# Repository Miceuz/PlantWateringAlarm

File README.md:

PlantWateringAlarm
==================

A soil moisture level sensor based on ATTINY44. Uses capacitive sensing.

More info at http://wemakethings.net/chirp

Contact: mic a wemakethings.net

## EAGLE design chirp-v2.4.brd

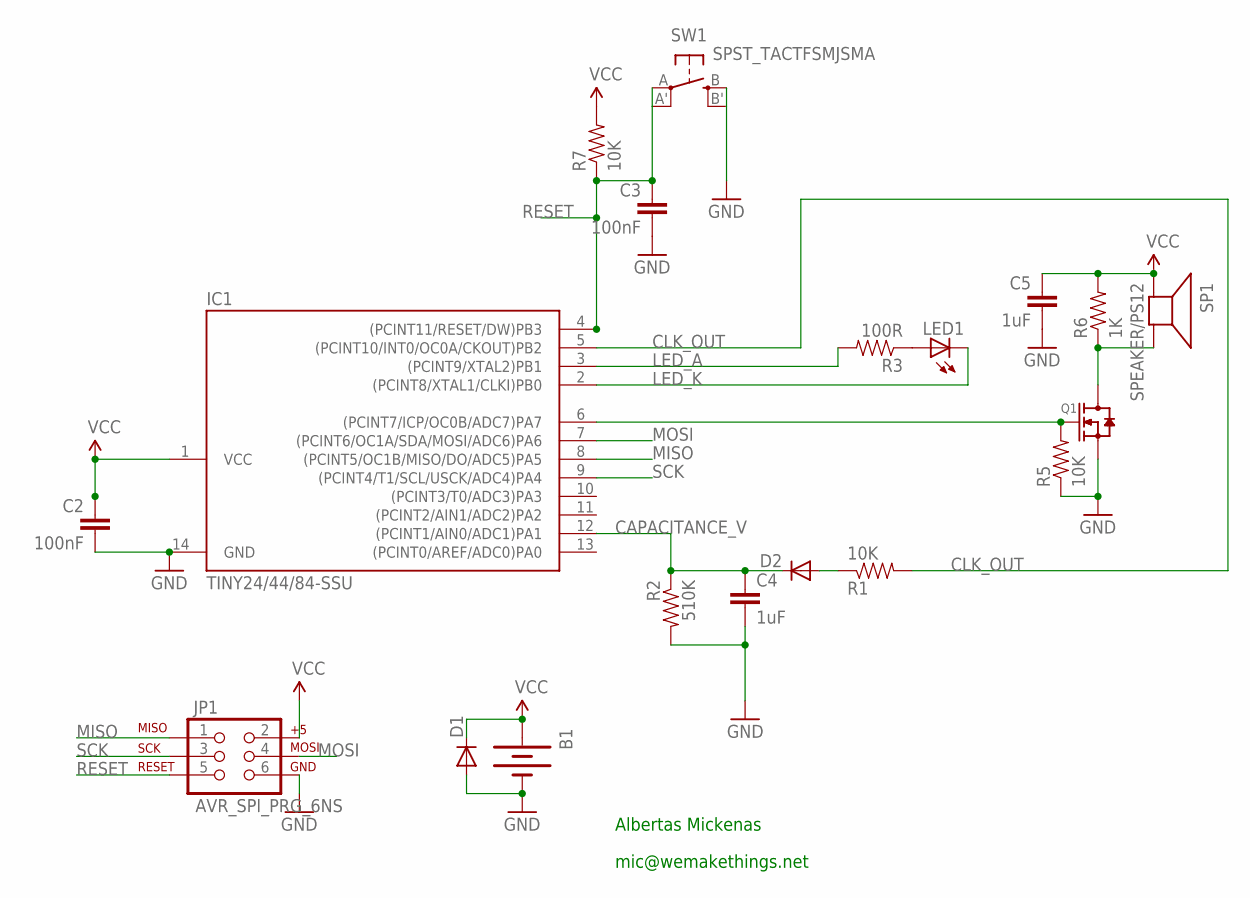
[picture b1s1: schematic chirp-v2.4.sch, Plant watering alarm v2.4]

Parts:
B1: BATTERY; BAT-HLD-001
C2, C3: 100nF; 0603-CAP
C4, C5: 1uF; 0603-CAP
D1: DIODE-DO214AC; DO214AC
D2: DIODE-SCHOTTKY_; SOD-523
IC1: TINY24/44/84-SSU; SOIC14
JP1: AVR_SPI_PRG_6NS; 2X3-NS
LED1: LEDCHIPLED_0805; CHIPLED_0805
Q1: MOSFET-N-SOT23; SOT23
R1, R5, R7: 10K; 0603-RES
R2: 510K; 0603-RES
R3: 100R; 0603-RES
R6: 1K; 0603-RES
SP1: SPEAKER/PS12; PS12
SW1: SPST_TACTFSMJSMA; FSMJSMA

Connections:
BUZZER: IC1.6 ((PCINT7/ICP/OC0B/ADC7)PA7), Q1.1 (G), R5.2
CAPACITANCE_V: C4.1, D2.K (C), IC1.12 ((PCINT1/AIN0/ADC1)PA1), R2.1
CLK_OUT: IC1.5 ((PCINT10/INT0/OC0A/CKOUT)PB2), R1.2
GND: B1.2 (-), C2.2, C3.2, C4.2, C5.2, D1.A, IC1.14 (GND), JP1.6, Q1.2 (S), R2.2, R5.1, SW1.B (S), SW1.B' (S1)
LED_A: IC1.3 ((PCINT9/XTAL2)PB1), R3.2
LED_K: IC1.2 ((PCINT8/XTAL1/CLKI)PB0), LED1.C
MISO: IC1.8 ((PCINT5/OC1B/MISO/DO/ADC5)PA5), JP1.1
MOSI: IC1.7 ((PCINT6/OC1A/SDA/MOSI/ADC6)PA6), JP1.4
unnamed: Q1.3 (D), R6.1, SP1.P$2 (-)
unnamed: LED1.A, R3.1
RESET: C3.1, IC1.4 ((PCINT11/RESET/DW)PB3), JP1.5, R7.1, SW1.A, SW1.A' (P1)
SCK: IC1.9 ((PCINT4/T1/SCL/USCK/ADC4)PA4), JP1.3
VCC: B1.1 (+), C2.1, C5.1, D1.C, IC1.1 (VCC), JP1.2, R6.2, R7.2, SP1.P$1 (+)
V_CAP: D2.A, R1.1

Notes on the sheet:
Albertas Mickenas
mic@wemakethings.net

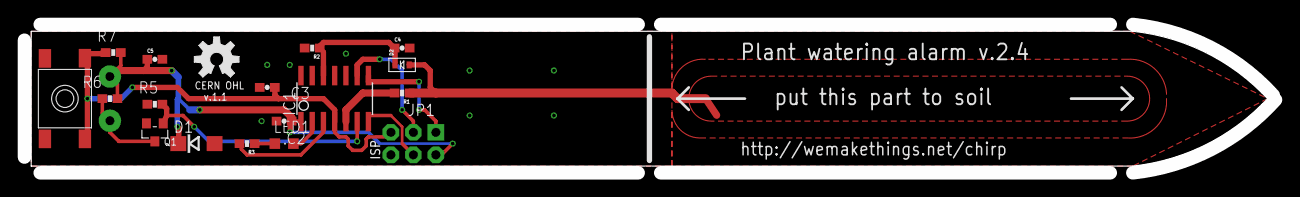
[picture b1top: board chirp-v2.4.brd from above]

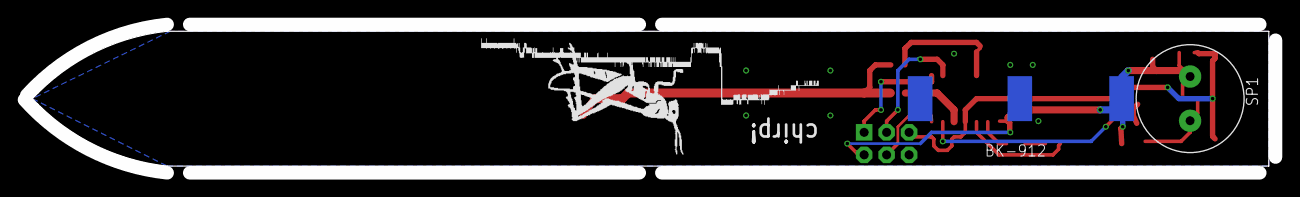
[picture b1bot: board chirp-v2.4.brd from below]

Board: 2 copper layers, 141.4 x 16.8 mm, 19 parts (2 on the bottom side), 14 nets.

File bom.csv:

IC1;Attiny44A;TINY24/44/84-SSU;SOIC-14;avr-5;DigiKey;ATTINY44A-SSU-ND;0.5595;32.36;http://www.atmel.com/Images/doc8183.pdf;main MCU;"44A is important as we need in ""low power"" variety"
SG1;;SPEAKER/PS12;PS12;adafruit;DigiKey;445-2525-1-ND;0.3392;19.62;http://www.tdk.co.jp/tefe02/ef532_ps.pdf;sound signal;can be replaced with cheaper one
B1;;BATTERY;BAT-HLD-001;SparkFun;DigiKey;BAT-HLD-001-ND;0.221;12.78;http://www.linxtechnologies.com/resources/diagrams/bat-hld-001.pdf;battery holder;
_B1;;battery;CR2032;;DigiKey;P189-ND;0.196;11.33;http://panasonic.com/industrial/includes/pdf/Panasonic_Lithi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;main battery;
D2;DIODE-SCHOTTKY;DIODESOD-523;SOD-523;microbuilder;DigiKey;RB751S40T1GOSCT-ND;0.099;5.73;http://www.onsemi.com/pub_link/Collateral/RB751S40T1-D.PDF;waveform rectification;should provide as low forward voltage drop as possible at low currents
S1;;TAC_SWITCHPTH;TACTILE-PTH;SparkFun;DigiKey;679-2428-ND;0.0771;4.46;http://www.apem.com/pdf/MJTP_6MM.pdf;reset switch;
Q1;;MOSFET-N-SOT23;SOT23;Seeed-Discrete;DigiKey;568-5818-1-ND;0.072;4.16;http://www.nxp.com/documents/data_sheet/2N7002P.pdf;buzzer switching;
LED1;;LEDCHIPLED_0805;CHIPLED_0805;adafruit;DigiKey;475-1410-1-ND;0.0637;3.68;"http://catalog.osram-os.com/catalogue/catalogue.do;jsessionid=B38D4035738FAE714C474120326E9384?act=downloadFile&favOid=02000002000009ee000100b6";Light level measurement, potentially indication;green is most sensitive to daylight, red - more broad spectrum
D1;;DIODE-SOD80C (DIODE-);SOD80C;diode;DigiKey;LL4148FSCT-ND;0.0384;2.22;http://www.fairchildsemi.com/ds/LL/LL4148.pdf;battery reverse polarity protection;must be capable of handling at least 20mA continuous current
C4;1uF;CAP0603-CAP;0603-CAP;SparkFun;DigiKey;399-3118-1-ND;0.019;1.1;;rectifier smoothing cap;
C5;1uF;CAP0603-CAP;0603-CAP;SparkFun;DigiKey;399-3118-1-ND;0.019;1.1;;power bypass;
C2;100nF;CAP0603-CAP;0603-CAP;SparkFun;DigiKey;478-1239-1-ND;0.00454;0.26;;decoupling;
C3;100nF;CAP0603-CAP;0603-CAP;SparkFun;DigiKey;478-1239-1-ND;0.00454;0.26;;decoupling;
R2;510K;RESISTOR0603-RES;0603-RES;SparkFun;DigiKey;311-510KGRCT-ND;0.0041;0.24;;low pass filter for rectified signal;
R3;100R;RESISTOR0603-RES;0603-RES;SparkFun;DigiKey;	311-100GRCT-ND;0.0041;0.24;;"
LED current limiting";
R6;1K;RESISTOR0603-RES;0603-RES;SparkFun;DigiKey;311-1.0KGRCT-ND;0.0041;0.24;;buzzer discharge;
R1;10K;RESISTOR0603-RES;0603-RES;SparkFun;DigiKey;P10KGTR-ND;0.00131;0.08;;low pass filter;might be adjusted depending on capacity of probe / clo
R5;10K;RESISTOR0603-RES;0603-RES;SparkFun;DigiKey;P10KGTR-ND;0.00131;0.08;;mosfet gate pulldown;
R7;10K;RESISTOR0603-RES;0603-RES;SparkFun;DigiKey;P10KGTR-ND;0.00131;0.08;;reset pullup;
JP1;AVR_SPI_PRG_6NS;AVR_SPI_PRG_6NS;2X3-NS;SparkFun;;;0;;;AVR ISP programming and SPI interface;just a footprint, not populated
;;;;;;;;;;;
;;;;;;Parts total:;1.72921;;;;
;;;;;;Parts + VAT;2.0577599;;;;
PCB;;;;;Seeed;;0.82;;;;
;;;;;;Total:;2.8777599;;;;
;;;;;;“+60%”;4.60441584;;;;
;;;;;;“+60%”;7.367065344;;;;
;;;;;;USD;9.6508556006;;;;

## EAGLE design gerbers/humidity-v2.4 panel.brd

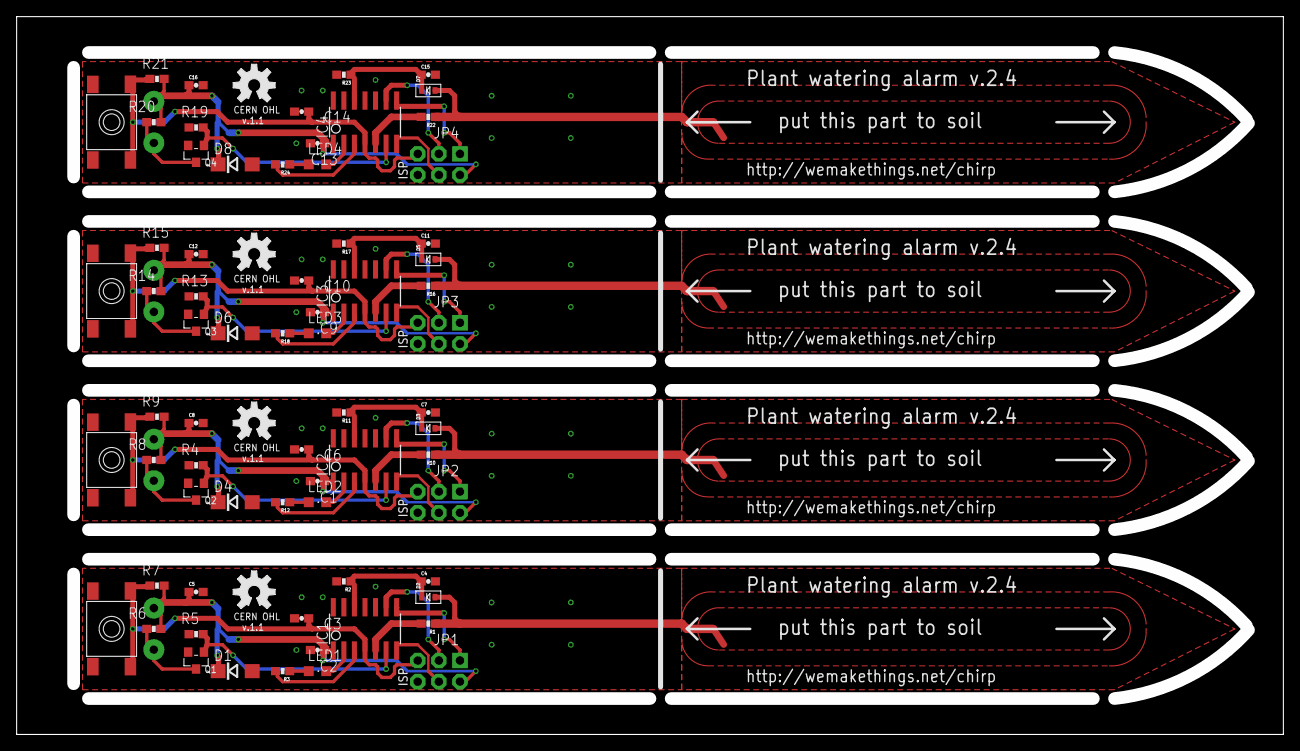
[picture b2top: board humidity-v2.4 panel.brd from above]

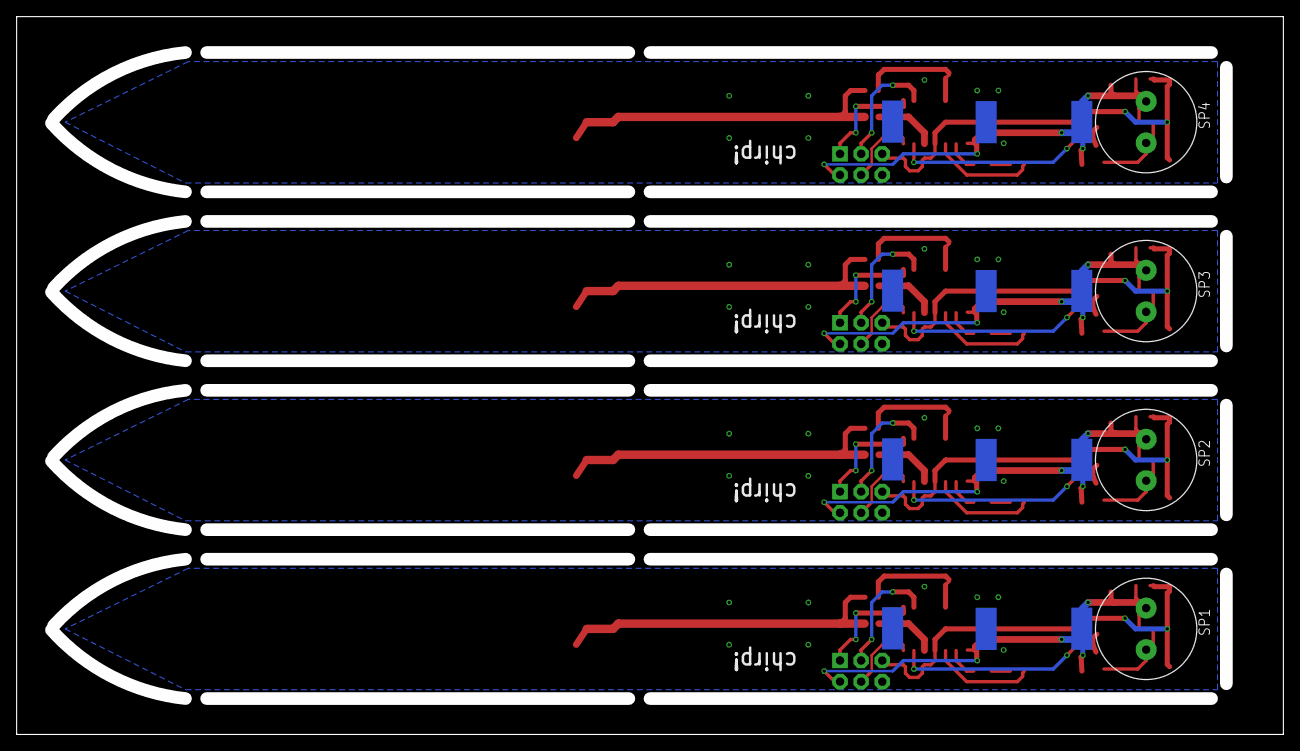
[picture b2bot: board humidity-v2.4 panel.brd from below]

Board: 2 copper layers, 152.4 x 86.4 mm, 76 parts (8 on the bottom side), 56 nets.

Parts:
B1, B2, B3, B4: BAT-HLD-001
C1, C2, C3, C6, C9, C10, C13, C14: 100nF; 0603-CAP
C4, C5, C7, C8, C11, C12, C15, C16: 1uF; 0603-CAP
D1, D4, D6, D8: DO214AC
D2, D3, D5, D7: DIODE-SCHOTTKY_; SOD-523
IC1, IC2, IC3, IC4: TINY24/44/84-SSU; SOIC14
JP1, JP2, JP3, JP4: AVR_SPI_PRG_6NS; 2X3-NS
LED1, LED2, LED3, LED4: CHIPLED_0805
Q1, Q2, Q3, Q4: SOT23
R1, R4, R5, R7, R9, R10, R13, R15, R16, R19, R21, R22: 10K; 0603-RES
R2, R11, R17, R23: 510K; 0603-RES
R3, R12, R18, R24: 100R; 0603-RES
R6, R8, R14, R20: 1K; 0603-RES
SP1, SP2, SP3, SP4: SPEAKER/PS12; PS12
SW1, SW2, SW3, SW4: SPST_TACTFSMJSMA; FSMJSMA

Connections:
BUZZER: IC1.6, Q1.1, R5.2
BUZZER1: IC2.6, Q2.1, R4.2
BUZZER2: IC3.6, Q3.1, R13.2
BUZZER3: IC4.6, Q4.1, R19.2
CAPACITANCE_V: C4.1, D2.K, IC1.12, R2.1
CAPACITANCE_V1: C7.1, D3.K, IC2.12, R11.1
CAPACITANCE_V2: C11.1, D5.K, IC3.12, R17.1
CAPACITANCE_V3: C15.1, D7.K, IC4.12, R23.1
CLK_OUT: IC1.5, R1.2
CLK_OUT1: IC2.5, R10.2
CLK_OUT2: IC3.5, R16.2
CLK_OUT3: IC4.5, R22.2
GND: B1.2, C2.2, C3.2, C4.2, C5.2, D1.A, IC1.14, JP1.6, Q1.2, R2.2, R5.1, SW1.B, SW1.B'
GND1: B2.2, C1.2, C6.2, C7.2, C8.2, D4.A, IC2.14, JP2.6, Q2.2, R4.1, R11.2, SW2.B, SW2.B'
GND2: B3.2, C9.2, C10.2, C11.2, C12.2, D6.A, IC3.14, JP3.6, Q3.2, R13.1, R17.2, SW3.B, SW3.B'
GND3: B4.2, C13.2, C14.2, C15.2, C16.2, D8.A, IC4.14, JP4.6, Q4.2, R19.1, R23.2, SW4.B, SW4.B'
LED_A: IC1.3, R3.2
LED_A1: IC2.3, R12.2
LED_A2: IC3.3, R18.2
LED_A3: IC4.3, R24.2
LED_K: IC1.2, LED1.C
LED_K1: IC2.2, LED2.C
LED_K2: IC3.2, LED3.C
LED_K3: IC4.2, LED4.C
MISO: IC1.8, JP1.1
MISO1: IC2.8, JP2.1
MISO2: IC3.8, JP3.1
MISO3: IC4.8, JP4.1
MOSI: IC1.7, JP1.4
MOSI1: IC2.7, JP2.4
MOSI2: IC3.7, JP3.4
MOSI3: IC4.7, JP4.4
unnamed: Q1.3, R6.1, SP1.P$2
unnamed: LED1.A, R3.1
unnamed: Q2.3, R8.1, SP2.P$2
unnamed: LED2.A, R12.1
unnamed: Q3.3, R14.1, SP3.P$2
unnamed: LED3.A, R18.1
unnamed: Q4.3, R20.1, SP4.P$2
unnamed: LED4.A, R24.1
RESET: C3.1, IC1.4, JP1.5, R7.1, SW1.A, SW1.A'
RESET1: C6.1, IC2.4, JP2.5, R9.1, SW2.A, SW2.A'
RESET2: C10.1, IC3.4, JP3.5, R15.1, SW3.A, SW3.A'
RESET3: C14.1, IC4.4, JP4.5, R21.1, SW4.A, SW4.A'
SCK: IC1.9, JP1.3
SCK1: IC2.9, JP2.3
SCK2: IC3.9, JP3.3
SCK3: IC4.9, JP4.3
VCC: B1.1, C2.1, C5.1, D1.C, IC1.1, JP1.2, R6.2, R7.2, SP1.P$1
VCC1: B2.1, C1.1, C8.1, D4.C, IC2.1, JP2.2, R8.2, R9.2, SP2.P$1
VCC2: B3.1, C9.1, C12.1, D6.C, IC3.1, JP3.2, R14.2, R15.2, SP3.P$1
VCC3: B4.1, C13.1, C16.1, D8.C, IC4.1, JP4.2, R20.2, R21.2, SP4.P$1
V_CAP: D2.A, R1.1
V_CAP1: D3.A, R10.1
V_CAP2: D5.A, R16.1
V_CAP3: D7.A, R22.1

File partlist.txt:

Partlist

Exported from humidity-v2.3.1.sch at 2013/04/15/ 8:11 PM

EAGLE Version 5.11.0 Copyright (c) 1988-2010 CadSoft

Part     Value            Device           Package      Library        Sheet

B1                        BATTERY          BAT-HLD-001  SparkFun       1
C2       100nF            CAP0603-CAP      0603-CAP     SparkFun       1
C3       100nF            CAP0603-CAP      0603-CAP     SparkFun       1
C4       1uF              CAP0603-CAP      0603-CAP     SparkFun       1
C5       1uF              CAP0603-CAP      0603-CAP     SparkFun       1
D1                        DIODE-SOD80C     SOD80C       diode          1
D2       DIODE-SCHOTTKY_  DIODESOD-523     SOD-523      microbuilder   1
IC1      TINY24/44/84-SSU TINY24/44/84-SSU SOIC14       avr-5          1
JP1      AVR_SPI_PRG_6NS  AVR_SPI_PRG_6NS  2X3-NS       SparkFun       1
LED1                      LEDCHIPLED_0805  CHIPLED_0805 adafruit       1
Q1                        MOSFET-N-SOT23   SOT23        Seeed-Discrete 1
R1       10K              RESISTOR0603-RES 0603-RES     SparkFun       1
R2       510K             RESISTOR0603-RES 0603-RES     SparkFun       1
R3       100R             RESISTOR0603-RES 0603-RES     SparkFun       1
R5       10K              RESISTOR0603-RES 0603-RES     SparkFun       1
R6       1K               RESISTOR0603-RES 0603-RES     SparkFun       1
R7       10K              RESISTOR0603-RES 0603-RES     SparkFun       1
S1                        TAC_SWITCHPTH    TACTILE-PTH  SparkFun       1
SP1      SPEAKER/PS12     SPEAKER/PS12     PS12         adafruit       1

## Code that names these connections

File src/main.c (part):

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#include <avr/eeprom.h>
#include "usiTwiSlave.h"

#define USI_SCK PA4
#define USI_MISO PA5
#define USI_CS PA6
#define BUZZER PA7
#define BUTTON PB2
#define LED_K PB0 
#define LED_A PB1

//------------ peripherals ----------------

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}

void inline ledOff() {
  DDRB &= ~(_BV(LED_A) | _BV(LED_K)); //make pins inputs
  PORTB &= ~(_BV(LED_A) | _BV(LED_K));//disable pullups
}

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    DDRA |= _BV(BUZZER);   //piezo buzzer
    PORTA &= ~_BV(BUZZER);
    
    DDRB |= _BV(PB0);   //nothing
    PORTB &= ~_BV(PB0);
    DDRB |= _BV(PB1);   //nothing
    PORTB &= ~_BV(PB1);
    DDRB |= _BV(PB2);   //square wave output
    PORTB &= ~_BV(PB2);
}

void inline setupPowerSaving() {
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    uint16_t result = getADC1();
    
    stopExcitationSignal();
    PORTB &= ~_BV(PB2);
    PRR |= _BV(PRTIM0);
    
    ADCSRA &=~ _BV(ADEN);
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    TCCR1A = 0;
    TCCR1B = _BV(CS12);					//start timer1 with prescaler clk/256
    
    PCMSK1 |= _BV(PCINT8); 				//enable pin change interrupt on LED_K
    GIMSK |= _BV(PCIE1); 
    lightCycleOver = 0;
    while(!lightCycleOver) {
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
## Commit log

2012-08-02 initial board and schematics
2012-08-02 git ignore
2012-09-07 +firmware, thicker traces, etc
2012-09-16 +power saving
2012-09-29 mainly current test setup code, some power saving directives commented out
2012-09-29 working on v2.1 and v2.2 - low pass filter based setup. various sensor designs for testing
2012-09-29 enable clock output on PB2
2012-09-30 defines for pins according to function
2012-10-03 all the v2.2 changes + light sensor
2012-10-23 v2.3 ordered from seeed
2012-10-23 Licensed under CERN OHL v.1.1
2012-11-28 final touches before production
2012-11-28 start working on finalization of firmware
2012-11-30 state machine implemented - 4 levels of operation depending how dry soil is
2012-11-30 ignore *i *s
2012-12-05 fiddling with the thresholds
2012-12-05 minor spelling fixes
2012-12-05 moved the insertion line a bit further, moved components away from the soil, made a new order at seeed
2012-12-05 more readme
2013-06-09 less frightened margins
2013-06-10 change SPI to I2C
2013-06-10 USI driver
2013-06-10 add schematics pic for eagle free people
2013-07-14 add twi driver to makefile
2013-07-14 fix thresholds, tune up sensor mode
2013-10-27 a new board design
2014-01-08 rollback previous commit to main.c as it was just testing mode code
2014-01-17 schematics png updated
2014-02-17 Don't switch OSC speed as it cretes problems in sensor mode. Run everything at 2Mhz. Chirp sound has changed, but oh well. Turn the thresholds all the way down. For plants that are watered more often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
2014-02-17 shuffle code around to look nicer
2014-02-17 put direcotry in to some order
2014-02-19 leave led connected to ground while discharging
2014-02-19 schematics in b/w
2014-04-28 quick and dirty sensor mode. works as expected
2014-05-04 code cleanup, fix so it realy works, light measurement is done asynchroneously
2014-05-13 fix a bug which prevented using I2C adresses with MSB set, probably it was because Arduino sets up SDA too soon and there is a shady STOP condition detection in START interrupt handler. Added more st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
2014-05-13 Don't blink leds as this interferes with light measurement
2014-05-17 v-scoring instead of routing
2014-08-05 Add bitrate setting to makefile
2014-09-03 Add sensor schematics and PCB drawings
2014-11-23 erase eeprom while flashing, allow eeprom erasing in fuses
2014-11-23 on the first startup expect full darkness and calibrate to that, save light threshold to eeprom
2014-11-24 let the light threshold be 10% from total darkness
2014-11-25 add programmer jig firmware
2014-11-25 add some pics
2014-11-29 finally I2C comm works. damn third party libraries
2014-11-29 add I2C command to return the firmware version
2014-11-29 add testing functionality, update firmware to sensor v2.1
2014-12-02 less wait before programming, put the right firmware image into the programmer
2015-03-10 Don't allow the address to be set 0
2015-07-02 Measure light less, smaller delay
2015-12-13 Be more verbose when avrduding
2015-12-13 Move Chirp layout to KiCad. Finally.
2016-02-23 Add manufacturing set, tune up the silkscreen on the board
2016-05-11 Some test data
2017-08-30 Fix inline function declarations, preserve eeprom upon flashing
2018-02-19 Add some means to detect battery level, not working yet
2018-03-13 Play around with excitation signal settings, make excitation signal start from the very begining, avoid long delays in capacitance measurement. Non working unfortunately
2018-03-13 Shorten the measurement time as we change the capacitor to a smaller one. Avoid ADC sleep as it stops the excitation timer
2018-03-22 Erase eeprom on reflash. Blink led before chirping
2018-03-23 Fix a bug with adc mux selection. Add debug output. Make it work? Maybe?
2018-03-23 Invert the capasitanceDiff logic, play with sleep time constants and thresholds, change the playHappy logic
2018-03-23 measure ref voltage during the whork also
2018-03-23 refactor battery measurement
2018-03-23 Refactor adcOn and Off, some small refactorings
2018-03-23 Refactor calibration routines and do full sleep outside of the if structure
2018-03-23 fix adc turn off by setuping power saving just before the main loop, set ref capacitance closest to measurement events so that it's more similar to initial measurements
2018-03-23 Firmatting fixes
2018-03-23 Make some functions inline, extract a playHappy method
2018-03-23 Even more inlining of functions
2018-03-23 Refactor the logic as a state machine in a switch statement. Expermental
2018-03-27 Refactor entering to hibernate
2018-03-27 Add soft uart library for debug purposes
2018-03-27 Allow newer C syntax, add debug output
2018-03-27 Add hardware changes - add U1 LDO regulator, connect ISP VCC to battery, update cap values, update footprints, update routing, update battery footprint
2019-02-23 Prohibit setting i2c addresses > 127
    i2c addresses are 7 bits, where the 8th bit is reserved by the protocol to indicate whether reading or writing is intended.
2020-04-08 Fix a grave bug where hibernate counter was 8bit when total counts were 16bit. Add debug printing for monitoring
2021-09-30 add missing include
2023-06-06 typos, twink
